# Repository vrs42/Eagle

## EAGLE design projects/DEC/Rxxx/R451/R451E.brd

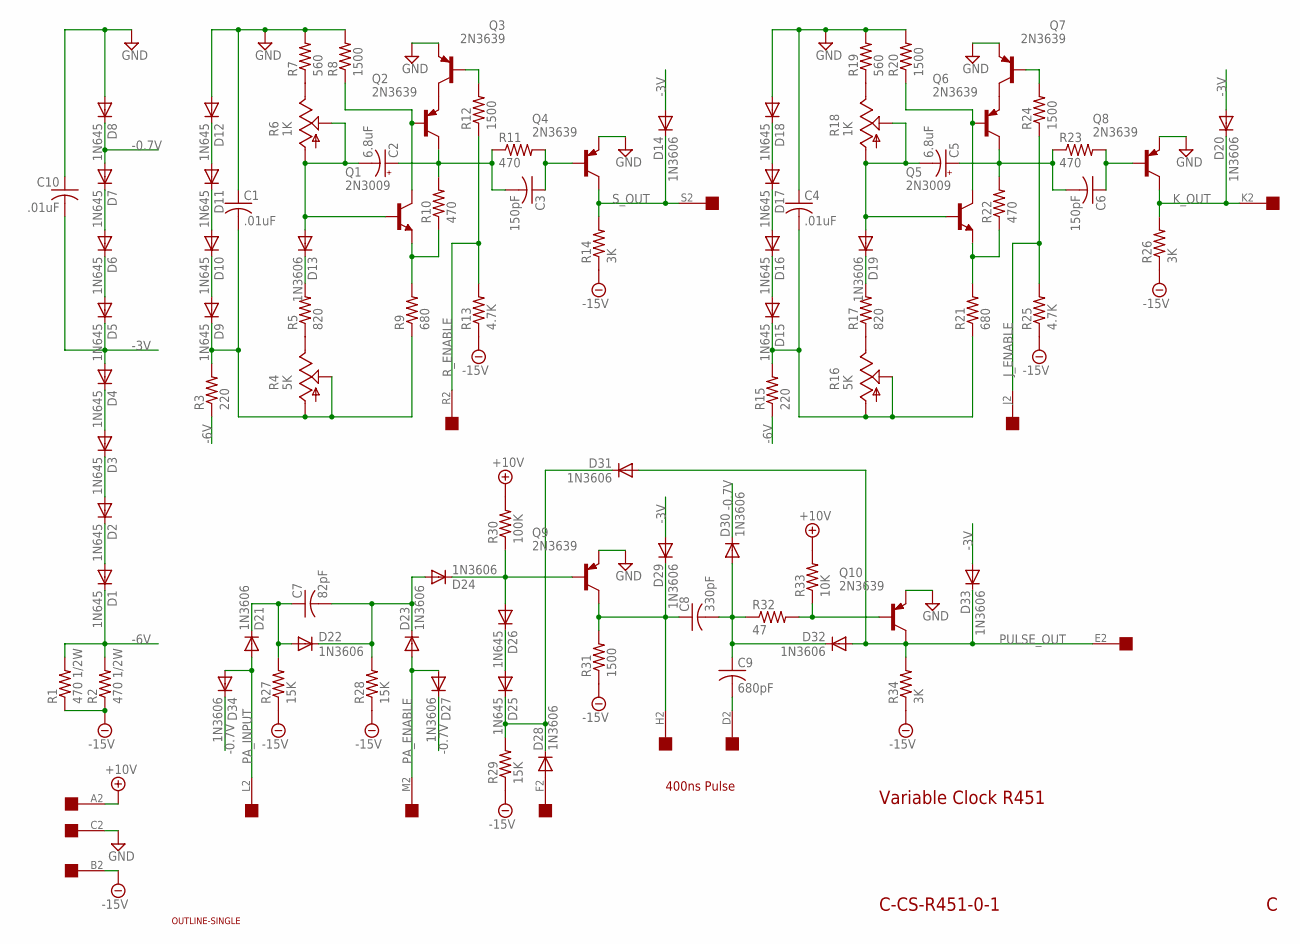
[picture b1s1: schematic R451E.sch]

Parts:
C1, C4, C10: .01uF; C050-025X075
C2, C5: 6.8uF; E12-4
C3, C6: 150pF; C075-032X103
C7: 82pF; C075-032X103
C8: 330pF; C075-032X103
C9: 680pF; C075-032X103
D1, D2, D3, D4, D5, D6, D7, D8, D9, D10, D11, D12, D15, D16, D17, D18, D25, D26: 1N645; DO35-10
D13, D14, D19, D20, D21, D22, D23, D24, D27, D28, D29, D30, D31, D32, D33, D34: 1N3606; DO35-10
Q1, Q5: 2N3009; TO5
Q2, Q3, Q4, Q6, Q7, Q8, Q9, Q10: 2N3639; TO39
R1, R2: 470 1/2W; 0411/15
R3, R15: 220; 0207/10
R4, R16: 5K; CT6
R5, R17: 820; 0207/10
R6, R18: 1K; CT6
R7, R19: 560; 0207/10
R8, R12, R20, R24, R31: 1500; 0207/10
R9, R21: 680; 0207/10
R10, R11, R22, R23: 470; 0207/10
R13, R25: 4.7K; 0207/10
R14, R26, R34: 3K; 0207/10
R27, R28, R29: 15K; 0207/10
R30: 100K; 0207/10
R32: 47; 0207/10
R33: 10K; 0207/10
U$1: OUTLINE-SINGLE; SINGLE
U$2: EDGE-1; EDGE-CON1

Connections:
+10V: R30.2, R33.2, U$2.A2
-0.7V: D7.A, D8.C, D27.C, D30.C, D34.C
-3V: C10.2, D4.A, D5.C, D14.A, D20.A, D29.A, D33.A
-6V: D1.C, R1.2, R2.2, R3.1, R15.1
-15V: R1.1, R2.1, R13.1, R14.1, R25.1, R26.1, R27.1, R28.1, R29.1, R31.1, R34.1, U$2.B2
GND: C1.1, C4.1, C10.1, D8.A, D12.A, D18.A, Q3.1 (E), Q4.1 (E), Q7.1 (E), Q8.1 (E), Q9.1 (E), Q10.1 (E), R7.2, R8.2, R19.2, R20.2, U$2.C2
J_ENABLE: R24.1, R25.2, U$2.J2
K_OUT: D20.C, Q8.3 (C), R26.2, U$2.K2
unnamed: D1.A, D2.C
unnamed: D5.A, D6.C
unnamed: D11.A, D12.C
unnamed: D10.A, D11.C
unnamed: D9.A, D10.C
unnamed: C1.2, D9.C, R3.2, R4.A, R4.S, R9.1
unnamed: Q1.1 (E), R9.2, R10.1
unnamed: R4.E, R5.1
unnamed: D13.C, R5.2
unnamed: C2.-, D13.A, Q1.2 (B), R6.A, R6.S
unnamed: Q1.3 (C), Q2.2 (B), R8.1
unnamed: C2.+, C3.2, Q2.3 (C), R10.2, R11.1
unnamed: D2.A, D3.C
unnamed: D3.A, D4.C
unnamed: Q3.2 (B), R12.2
unnamed: Q2.1 (E), Q3.3 (C)
unnamed: R6.E, R7.1
unnamed: C3.1, Q4.2 (B), R11.2
unnamed: D17.A, D18.C
unnamed: D16.A, D17.C
unnamed: D15.A, D16.C
unnamed: C4.2, D15.C, R15.2, R16.A, R16.S, R21.1
unnamed: D19.C, R17.2
unnamed: D28.A, U$2.F2
unnamed: Q5.1 (E), R21.2, R22.1
unnamed: C7.1, D21.C, D22.A, R27.2
unnamed: C5.-, D19.A, Q5.2 (B), R18.A, R18.S
unnamed: C7.2, D22.C, D23.C, D24.A, R28.2
unnamed: Q5.3 (C), Q6.2 (B), R20.1
unnamed: Q6.1 (E), Q7.3 (C)
unnamed: R18.E, R19.1
unnamed: R16.E, R17.1
unnamed: C5.+, C6.2, Q6.3 (C), R22.2, R23.1
unnamed: C6.1, Q8.2 (B), R23.2
unnamed: Q7.2 (B), R24.2
unnamed: C8.1, D29.C, Q9.3 (C), R31.2, U$2.H2
unnamed: D24.C, D26.A, Q9.2 (B), R30.1
unnamed: D25.A, D26.C
unnamed: D25.C, D28.C, D31.C, R29.2
unnamed: C8.2, C9.1, D30.A, D32.C, R32.1
unnamed: C9.2, U$2.D2
unnamed: Q10.2 (B), R32.2, R33.1
unnamed: D6.A, D7.C
PA_ENABLE: D23.A, D27.A, U$2.M2
PA_INPUT: D21.A, D34.A, U$2.L2
PULSE_OUT: D31.A, D32.A, D33.C, Q10.3 (C), R34.2, U$2.E2
R_ENABLE: R12.1, R13.2, U$2.R2
S_OUT: D14.C, Q4.3 (C), R14.2, U$2.S2

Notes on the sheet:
Variable Clock R451
C-CS-R451-0-1
400ns Pulse

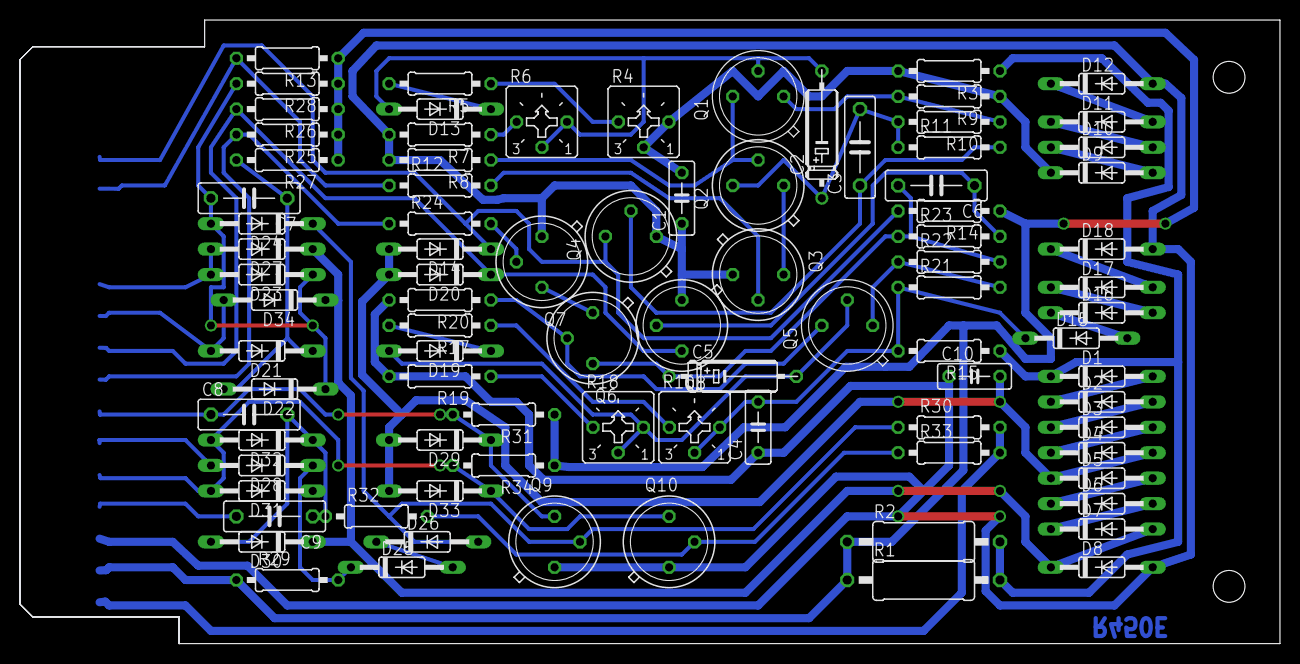
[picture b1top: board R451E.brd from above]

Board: 2 copper layers, 125.7 x 62.2 mm, 90 parts (0 on the bottom side), 56 nets.

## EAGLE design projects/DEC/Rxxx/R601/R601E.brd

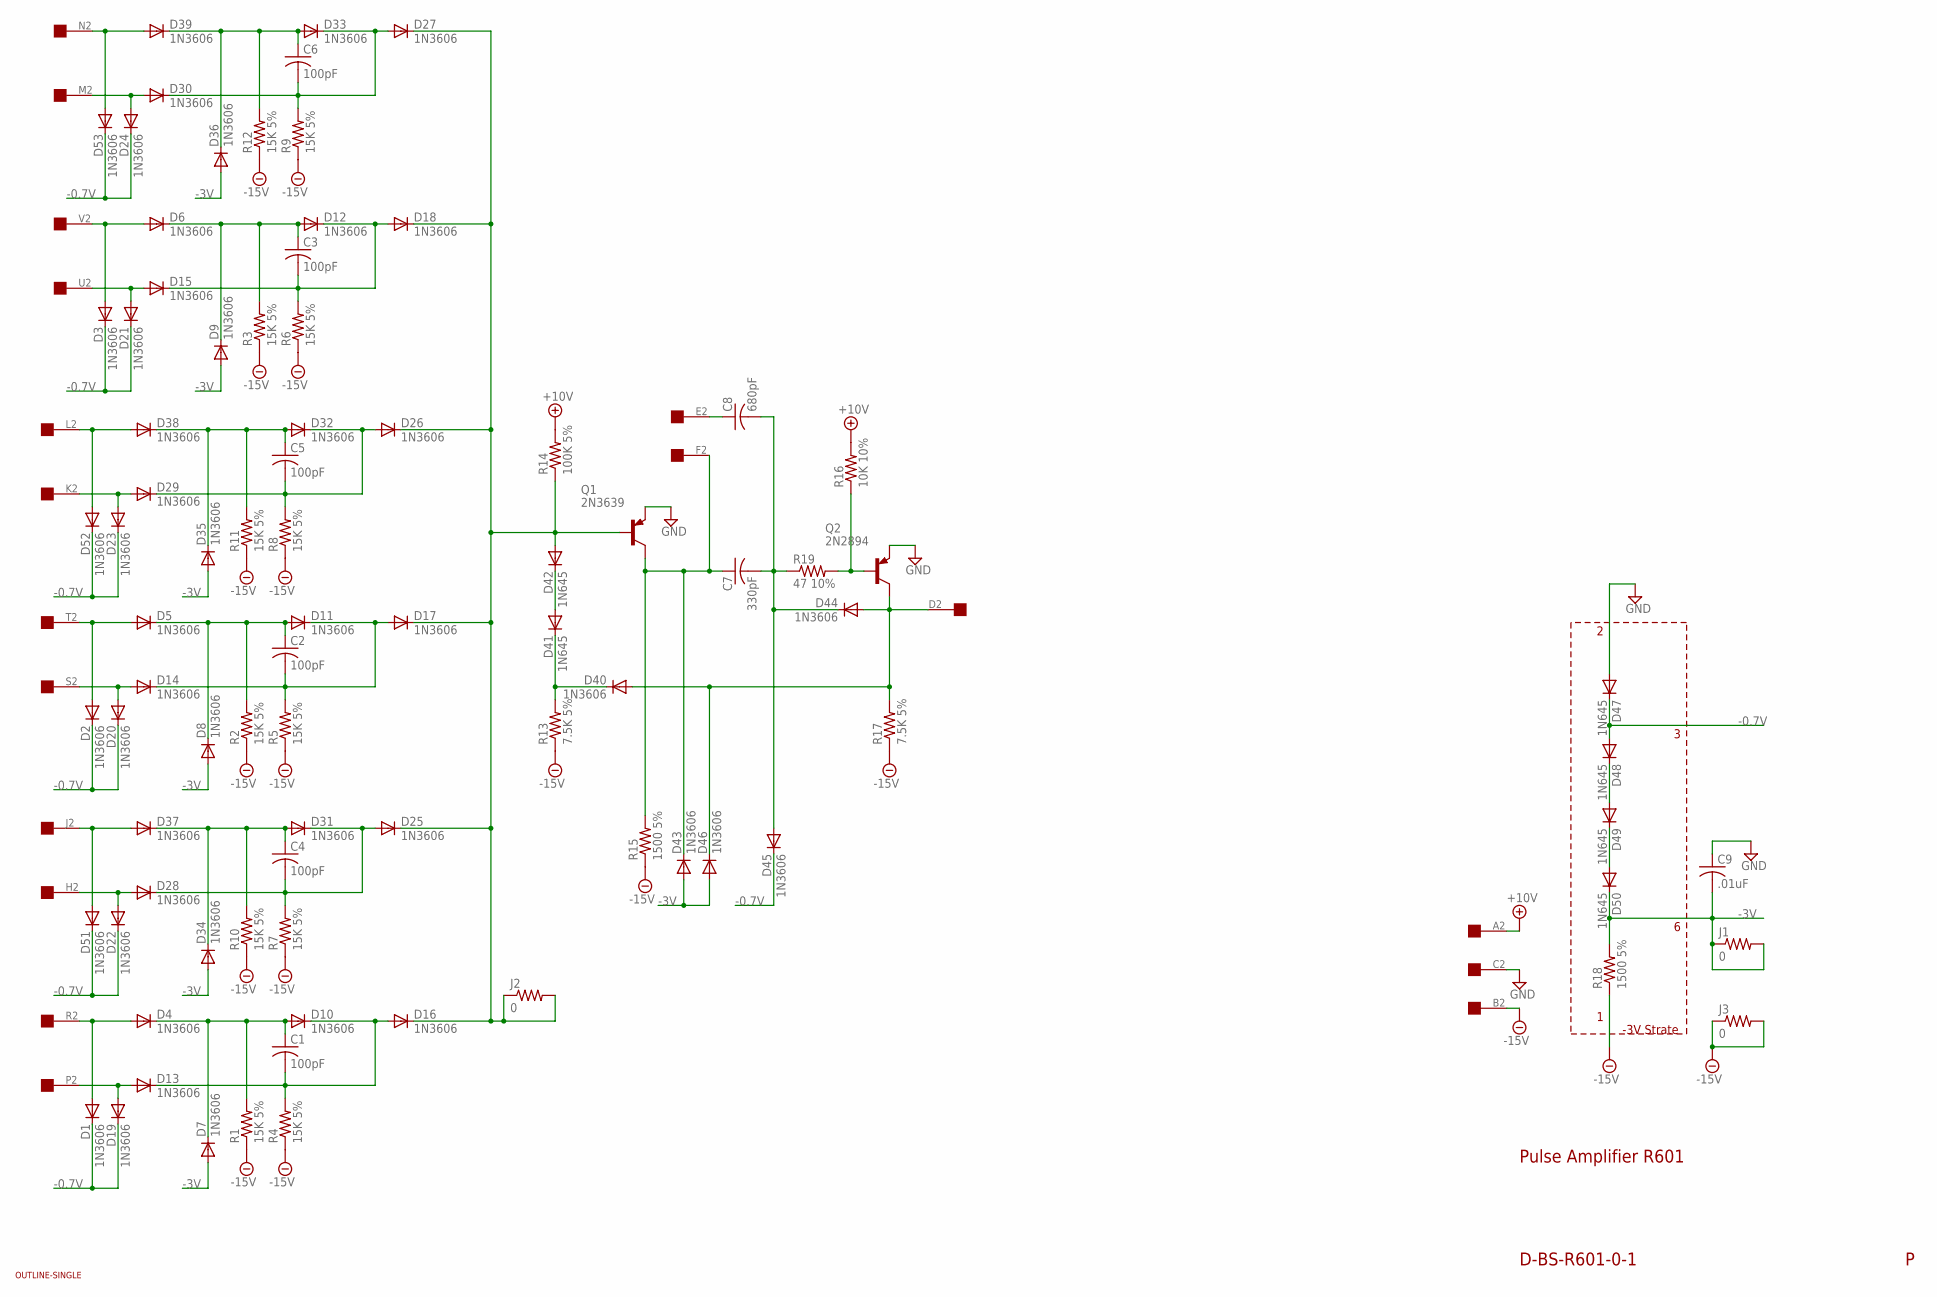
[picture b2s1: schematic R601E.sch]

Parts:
C1, C2, C3, C4, C5, C6: 100pF; C063-025X075
C7: 330pF; C063-025X075
C8: 680pF; C063-025X075
C9: .01uF; C063-025X075
D1, D2, D3, D4, D5, D6, D7, D8, D9, D10, D11, D12, D13, D14, D15, D16, D17, D18, D19, D20, D21, D22, D23, D24, D25, D26, D27, D28, D29, D30, D31, D32, D33, D34, D35, D36, D37, D38, D39, D40, D43, D44, D45, D46, D51, D52, D53: 1N3606; DO35-10
D41, D42, D47, D48, D49, D50: 1N645; DO35-10
J1, J2, J3: 0; 0207/10
Q1: 2N3639; TO39
Q2: 2N2894; TO39
R1, R2, R3, R4, R5, R6, R7, R8, R9, R10, R11, R12: 15K 5%; 0207/10
R13, R17: 7.5K 5%; 0207/10
R14: 100K 5%; 0207/10
R15, R18: 1500 5%; 0207/10
R16: 10K 10%; 0207/10
R19: 47 10%; 0207/10
U$1: OUTLINE-SINGLE; SINGLE
U$2: EDGE-1; EDGE-CON1

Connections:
+10V: R14.2, R16.2, U$2.A2
-0.7V: D1.C, D2.C, D3.C, D19.C, D20.C, D21.C, D22.C, D23.C, D24.C, D45.C, D47.C, D48.A, D51.C, D52.C, D53.C
-3V: C9.2, D7.A, D8.A, D9.A, D34.A, D35.A, D36.A, D43.A, D46.A, D50.C, J1.1, J1.2, R18.2
-15V: J3.1, J3.2, R1.1, R2.1, R3.1, R4.1, R5.1, R6.1, R7.1, R8.1, R9.1, R10.1, R11.1, R12.1, R13.1, R15.1, R17.1, R18.1, U$2.B2
GND: C9.1, D47.A, Q1.1 (E), Q2.1 (E), U$2.C2
unnamed: D37.A, D51.A, U$2.J2
unnamed: D40.C, D41.C, R13.2
unnamed: D39.A, D53.A, U$2.N2
unnamed: D24.A, D30.A, U$2.M2
unnamed: C6.1, D33.A, D36.C, D39.C, R12.2
unnamed: C6.2, D27.A, D30.C, D33.C, R9.2
unnamed: D41.A, D42.C
unnamed: D48.C, D49.A
unnamed: D49.C, D50.A
unnamed: D16.C, D17.C, D18.C, D25.C, D26.C, D27.C, D42.A, J2.1, J2.2, Q1.2 (B), R14.1
unnamed: C7.1, D43.C, Q1.3 (C), R15.2, U$2.F2
unnamed: C7.2, C8.2, D44.C, D45.A, R19.1
unnamed: Q2.2 (B), R16.1, R19.2
unnamed: D40.A, D44.A, D46.C, Q2.3 (C), R17.2, U$2.D2
unnamed: D3.A, D6.A, U$2.V2
unnamed: D15.A, D21.A, U$2.U2
unnamed: C3.1, D6.C, D9.C, D12.A, R3.2
unnamed: C3.2, D12.C, D15.C, D18.A, R6.2
unnamed: D38.A, D52.A, U$2.L2
unnamed: D23.A, D29.A, U$2.K2
unnamed: C5.1, D32.A, D35.C, D38.C, R11.2
unnamed: C5.2, D26.A, D29.C, D32.C, R8.2
unnamed: D22.A, D28.A, U$2.H2
unnamed: C4.1, D31.A, D34.C, D37.C, R10.2
unnamed: C4.2, D25.A, D28.C, D31.C, R7.2
unnamed: D1.A, D4.A, U$2.R2
unnamed: D13.A, D19.A, U$2.P2
unnamed: C1.1, D4.C, D7.C, D10.A, R1.2
unnamed: C1.2, D10.C, D13.C, D16.A, R4.2
unnamed: C8.1, U$2.E2
unnamed: D2.A, D5.A, U$2.T2
unnamed: D14.A, D20.A, U$2.S2
unnamed: C2.1, D5.C, D8.C, D11.A, R2.2
unnamed: C2.2, D11.C, D14.C, D17.A, R5.2

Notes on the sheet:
Pulse Amplifier R601
D-BS-R601-0-1
-3V Strate

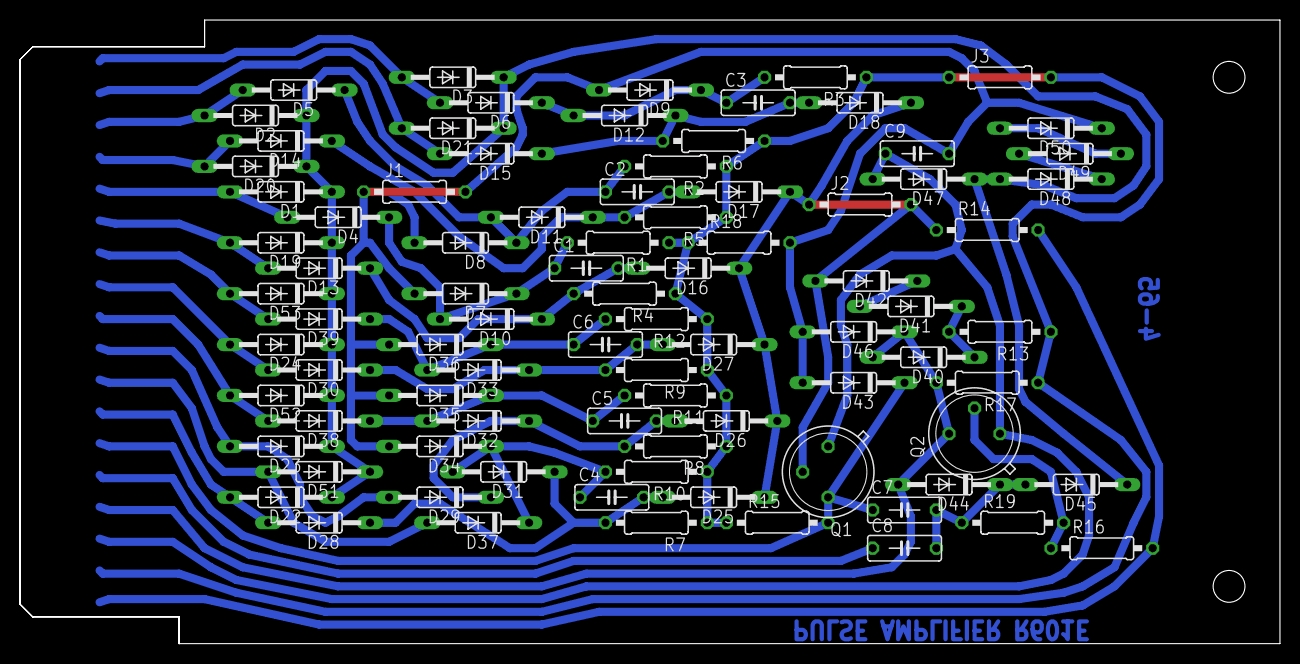
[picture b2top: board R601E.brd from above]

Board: 2 copper layers, 125.7 x 62.2 mm, 88 parts (0 on the bottom side), 39 nets.

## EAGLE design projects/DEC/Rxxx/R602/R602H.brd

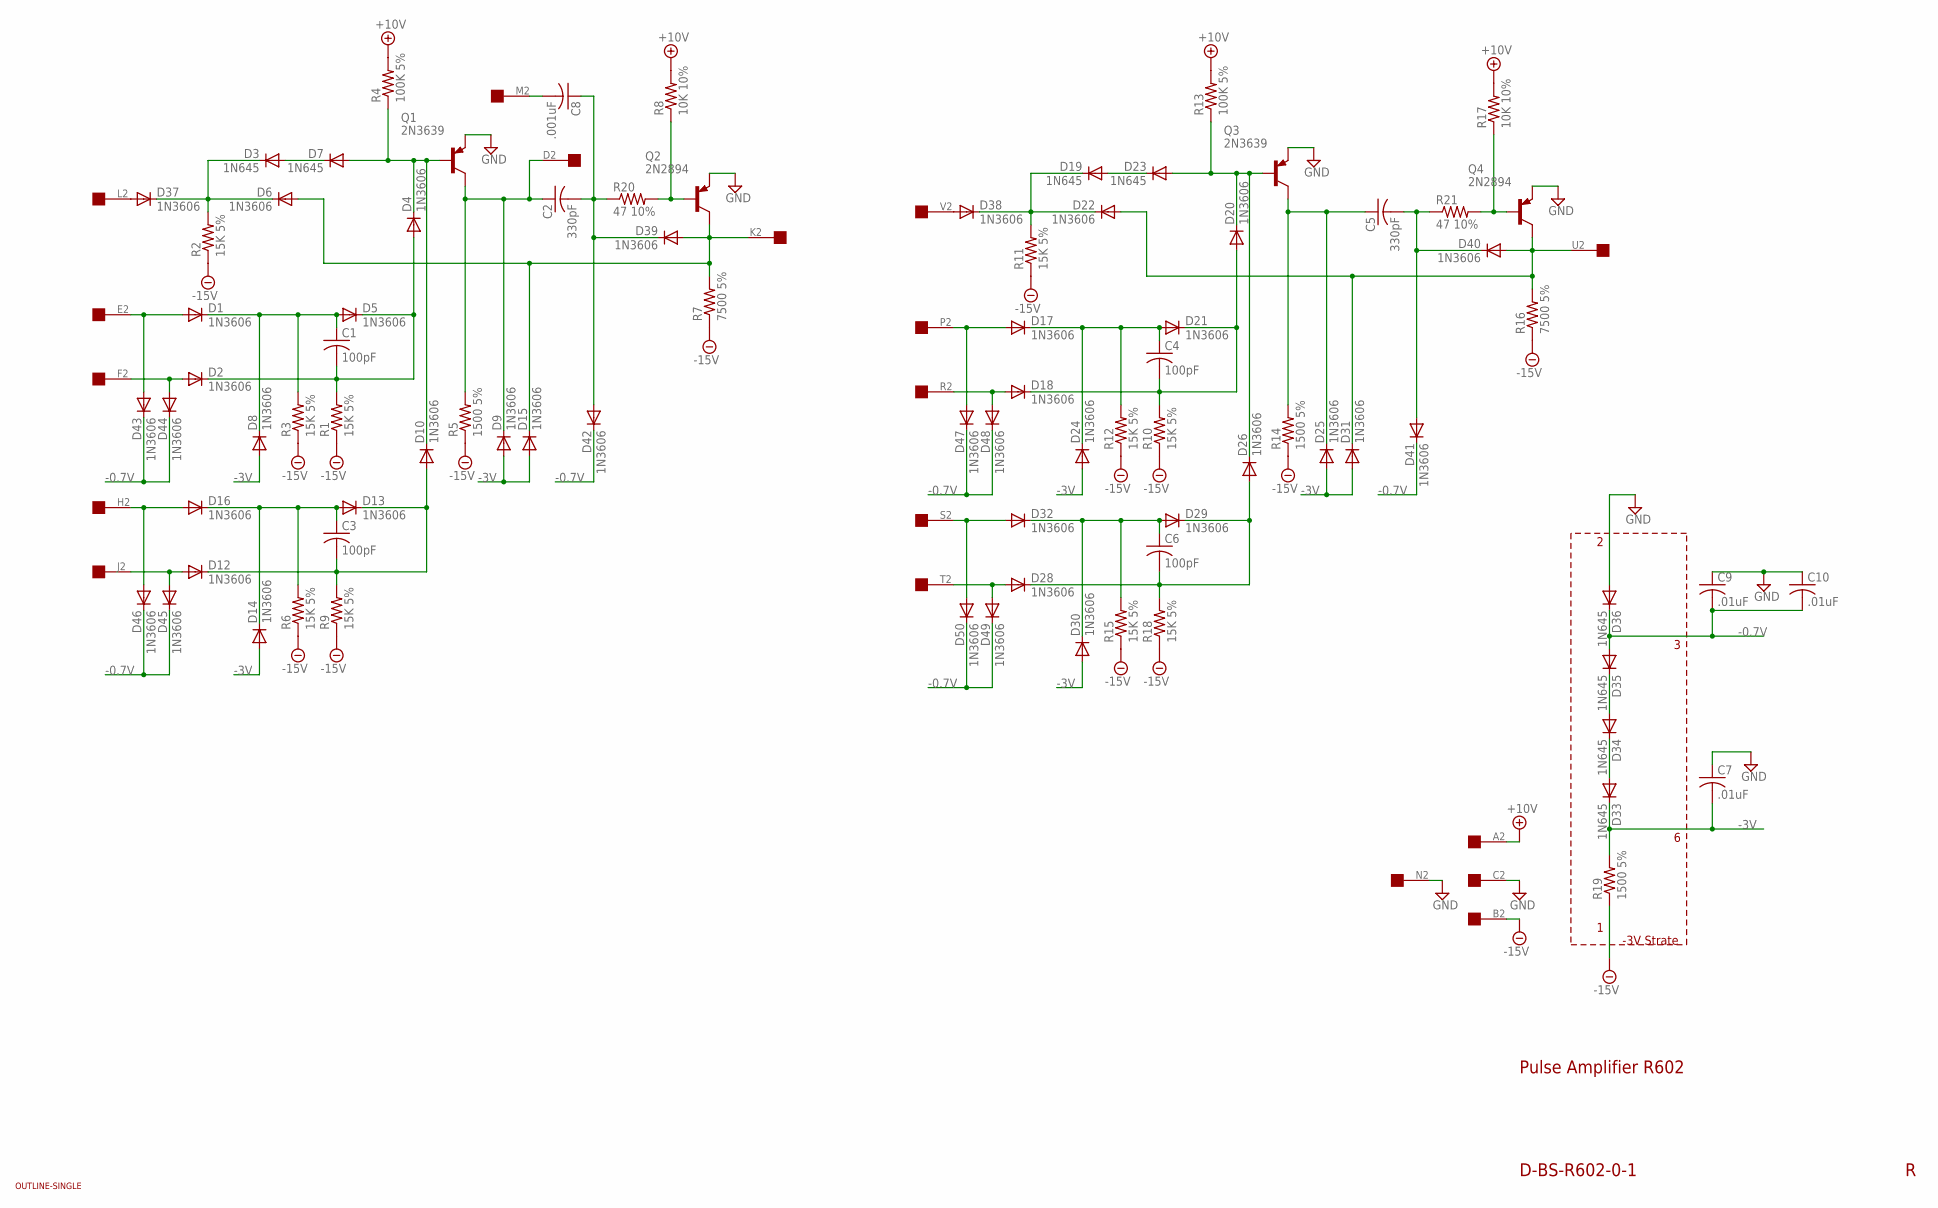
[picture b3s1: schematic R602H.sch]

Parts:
C1, C3, C4, C6: 100pF; C050-025X075
C2, C5: 330pF; C050-025X075
C7: .01uF; C075-032X103
C8: .001uF; C050-025X075
C9, C10: .01uF; C050-025X075
D1, D2, D4, D5, D6, D8, D9, D10, D12, D13, D14, D15, D16, D17, D18, D20, D21, D22, D24, D25, D26, D28, D29, D30, D31, D32, D37, D38, D39, D40, D41, D42, D43, D44, D45, D46, D47, D48, D49, D50: 1N3606; DO35-10
D3, D7, D19, D23, D33, D34, D35, D36: 1N645; DO35-10
Q1, Q3: 2N3639; TO39
Q2, Q4: 2N2894; TO39
R1, R2, R3, R6, R9, R10, R11, R12, R15, R18: 15K 5%; 0207/10
R4, R13: 100K 5%; 0207/10
R5, R14, R19: 1500 5%; 0207/10
R7, R16: 7500 5%; 0207/10
R8, R17: 10K 10%; 0207/10
R20, R21: 47 10%; 0207/10
U$1: OUTLINE-SINGLE; SINGLE
U$2: EDGE-1; EDGE-CON1

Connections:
+10V: R4.2, R8.2, R13.2, R17.2, U$2.A2
-0.7V: C9.2, C10.2, D35.A, D36.C, D41.C, D42.C, D43.C, D44.C, D45.C, D46.C, D47.C, D48.C, D49.C, D50.C
-3V: C7.2, D8.A, D9.A, D14.A, D15.A, D24.A, D25.A, D30.A, D31.A, D33.C, R19.2
-15V: R1.1, R2.1, R3.1, R5.1, R6.1, R7.1, R9.1, R10.1, R11.1, R12.1, R14.1, R15.1, R16.1, R18.1, R19.1, U$2.B2
GND: C7.1, C9.1, C10.1, D36.A, Q1.1 (E), Q2.1 (E), Q3.1 (E), Q4.1 (E), U$2.C2, U$2.N2
unnamed: D37.A, U$2.L2
unnamed: D3.C, D6.C, D37.C, R2.2
unnamed: D1.A, D43.A, U$2.E2
unnamed: D2.A, D44.A, U$2.F2
unnamed: C1.1, D1.C, D5.A, D8.C, R3.2
unnamed: C1.2, D2.C, D4.A, D5.C, R1.2
unnamed: D3.A, D7.C
unnamed: D34.A, D35.C
unnamed: D33.A, D34.C
unnamed: D4.C, D7.A, D10.C, Q1.2 (B), R4.1
unnamed: C2.1, D9.C, Q1.3 (C), R5.2, U$2.D2
unnamed: C2.2, C8.1, D39.C, D42.A, R20.1
unnamed: Q2.2 (B), R8.1, R20.2
unnamed: D6.A, D15.C, D39.A, Q2.3 (C), R7.2, U$2.K2
unnamed: D16.A, D46.A, U$2.H2
unnamed: D12.A, D45.A, U$2.J2
unnamed: C3.1, D13.A, D14.C, D16.C, R6.2
unnamed: C3.2, D10.A, D12.C, D13.C, R9.2
unnamed: D17.A, D47.A, U$2.P2
unnamed: D18.A, D48.A, U$2.R2
unnamed: C4.1, D17.C, D21.A, D24.C, R12.2
unnamed: C4.2, D18.C, D20.A, D21.C, R10.2
unnamed: D38.A, U$2.V2
unnamed: D19.C, D22.C, D38.C, R11.2
unnamed: D19.A, D23.C
unnamed: D20.C, D23.A, D26.C, Q3.2 (B), R13.1
unnamed: C5.1, D25.C, Q3.3 (C), R14.2
unnamed: C5.2, D40.C, D41.A, R21.1
unnamed: Q4.2 (B), R17.1, R21.2
unnamed: D22.A, D31.C, D40.A, Q4.3 (C), R16.2, U$2.U2
unnamed: D32.A, D50.A, U$2.S2
unnamed: D28.A, D49.A, U$2.T2
unnamed: C6.1, D29.A, D30.C, D32.C, R15.2
unnamed: C6.2, D26.A, D28.C, D29.C, R18.2
unnamed: C8.2, U$2.M2

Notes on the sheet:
Pulse Amplifier R602
D-BS-R602-0-1
-3V Strate

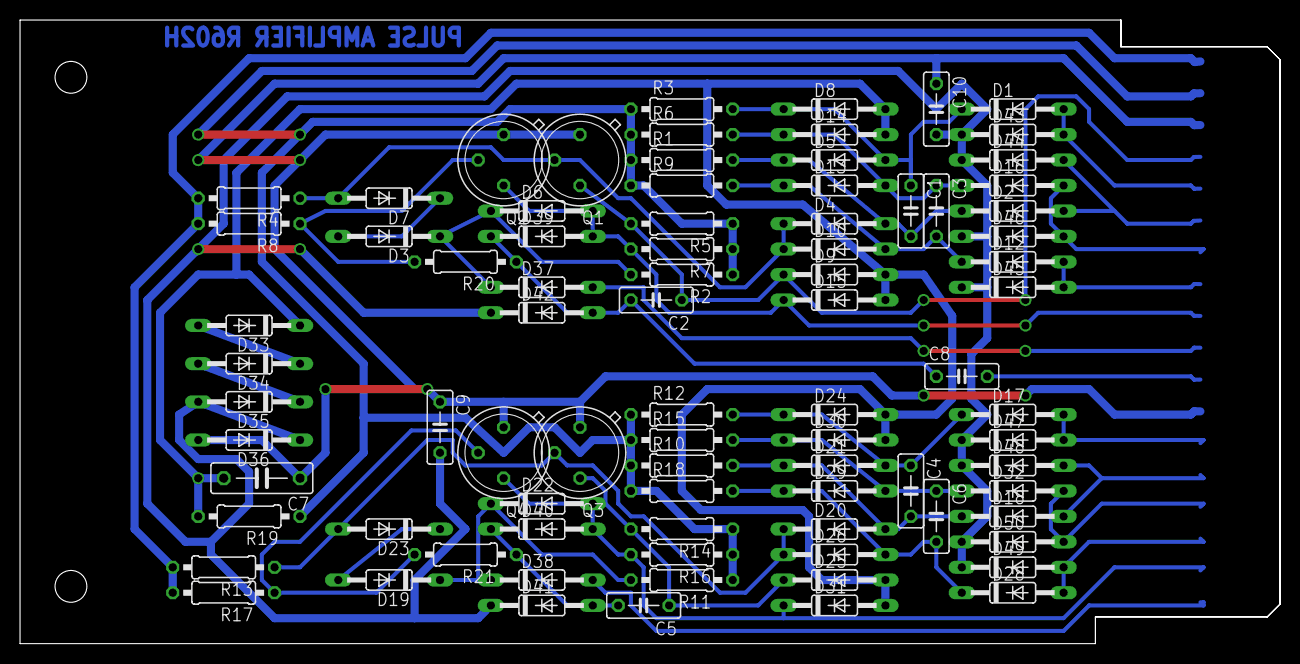
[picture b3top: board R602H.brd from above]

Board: 2 copper layers, 125.7 x 62.2 mm, 85 parts (0 on the bottom side), 40 nets.
